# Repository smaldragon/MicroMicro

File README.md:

# MicroMicro

The MicroMicro (working name) is a project designed for a series I inteded(intend) to write, about how microcomputers work and how to go about developing one. It was designed to use a relatively small amount of integrated circuits (13), not use any programmable chips, microcontrollers or obselete parts, and to be a self-contained architecture that handles its own input and output (ie. not serial based).

With these requirements in mind, the overall specs are humble but capable:
* an 65c02 8bit cpu, running at 2Mhz
* 32KiB of ram, 8K of which are video ram
* 256x240 black and white display, via vga
* 1bit "beeper" audio
* Ultra-compact 30 Key keyboard using the "gherkin" layout
* Tape Interface for loading and storing data
* Cartridge port for rom programs and peripheral expansion
* 2 atari-style joystick ports

*Potential Features*
* custom case made from pcbs

The software side is still up in the air, but I'm aiming for the following features:
* A text editor
* An high-level programming language (undecided on which)
* A built-in assembler
* Saving and loading via the tape interface

This code would likely be custom and documented to follow the article structure of the hardware side of things.

# Memory Map

```
+---------------------+-------+-----------+
| Name                | Size  | Location  |
+---------------------+-------+-----------+
| Zero Page & Stack   | 512   | 0000-01FF |
| Video Data          | 7680  | 0200-1FFF |
| General Purpose RAM | 24576 | 2000-7FFF |
| IO Registers        | 8192  | 8000-9FFF |
| Expansion ROM       | 8192  | C000-DFFF |
| Bios ROM            | 8192  | E000-FFFF |
+---------------------+-------+-----------+ 
* the area from A000-BFFF is an invalid bus conflict region
```

## Video Data Format

Each byte corresonds to a line of 8 horizontal pixels on the screen. The screen addresses are organized as 32x30 character cells of 8x8 pixels each. 8 Consecutive bytes build one character.

This non-linear format was chosen to speed up the rendering of characters to the screen.

## Keyboard and Joystick

The state of the keyboard and joysticks can be read at the following addresses:

```
+---------------------+----------+-------------------------+
| Name                | Address  | Value (bits 0-5)        |
+---------------------+----------+-------------------------+
| Keyboard Col 1      |   9FFE   |  Q   A  Shf  z   S   W  |
| Keyboard Col 2      |   9FFD   |  E   D   X   C   F   R  |
| Keyboard Col 3      |   9FFB   |  T   G   V   B   H   Y  |
| Keyboard Col 4      |   9FF7   |  U   J   N   M   K   I  |
| Keyboard Col 5      |   9FEF   |  O   L  SPC ALT ENT  P  |
| Joystick 1          |   8FFF   |  ↑   ↓   ←   →   L   R  |
| Joystick 2          |   97FF   |  ↑   ↓   ←   →   L   R  |
+---------------------+----------+-------------------------+
```

## Beeper and Tape Interface

The Beeper is a 1bit register that is used for both audio generation and to load and save programs to tape. It can be accessed through the following registers:

```
+---------------------+-------------+-----------+
| Name                | Address     | Value     |
+---------------------+-------------+-----------+
| State               | 9FFF (read) | TB.. .... |
| Toggle Beeper       | FFFF (write)| 0000 0000 |
+---------------------+-------------+-----------+
T = Tape Input
B = Beeper State (top 2 bits of input register)
```

The tape interface is a 4-pin trs connector that be connected directly to a computer using an appropriate aux cable.

> Note: While these registers can be accessed from alternative locations, the addresses and values on this table ensure no bus conflicts occur.

## Expansion Interface

The MicroMicro has an expansion interface that allows extending the base capabilities of the system in various ways:

## Generic Banked Expansion Rom

An 8KiB region is set aside in the memory map for expansion roms (`$C000-$DFFF`), the emulator implements a simple banked rom cartridge where the current bank can be switched by reading from `$A0xx`, where `xx` is the bank number, the selected bank is also automatically set to zero on reset.

The bios will automatically jump to address `$C008` on boot if it detects an expansion rom that begins with the sring `CART-RUN`.

Currently expansion roms can be loaded by dragging and dropping a file into the emulator window.

## IC List

The design uses only 12 integrated circuits:

* `65c02` - 8bit CPU
* `62256` - 32KiB SRAM
* `39SF010 or 28C64 or 27C256` - 8KiB Program ROM
* `74hc10` - Tripple 3inNAND
* `74hc14` - Hex inverter
* `74hc32` - Quad 2inOR
* `74hc166` - 8bit parallel-to-serial shift register
* `74hc174` - 6bit d-type latch
* `74hc541` - 8bit buffer
* `74hc590`*2 - 8bit Counters
* `74hc4520`- Dual 4bit Counters

# Operating System

The 8k bios provides a simple command line operating system with the following commands:

| Command               | Description                                    |
| --------------------- | ---------------------------------------------- |
| `help`                | Lists all available commands                   |
| `clear`               | Clears the display                             |
| `file`                | The Size and Name of the currently loaded file |
| `new`                 | Create a new file                              |
| `name <name>`         | Rename the current file                        |
| `edit`                | Open the file editor                           |
| `save`                | Save file to tape                              |
| `load`                | Load file from tape                            |
| `run`    	            | Run Loaded File                                |
| `peek <addr> <bytes>` | Read contents of Memory                        |
| `poke <addr> <bytes>` | Write to Memory                                |
| `prun <addr>`         | Run a Machine Code Subroutine                  |

More info on the bios can be found [here](Docs/bios.md)

# Changelog

## A2

[Interactive BOM](https://raw.githack.com/smaldragon/MicroMicro/refs/heads/main/Kicad/a2/bom/ibom.html)

* Reset is now performed using a MCP-100 voltage supervisor, this primarly serves to replace the 74HC14 Schmitt Trigger Hex NOT with a 74HCT04, reducing delays, improving reliabiliy of the clock oscillator circuit, and freeing 1 NOT gate for the video circuit
* Video glitches (leftmost pixel column doubled on right, junk at the bottom of the screen) are now gone
* VGA video output is now better centered on the screen
* The small 6mm buzzer has been replaced with an header for a small speaker, improving volume and sound clarity
* Filtering capacitor added to data output
* Needless diodes removed
* Fixed footprint for headphone jack
* 2 additional M2 screw posts added to the center region of the board
* Schematic rearranged

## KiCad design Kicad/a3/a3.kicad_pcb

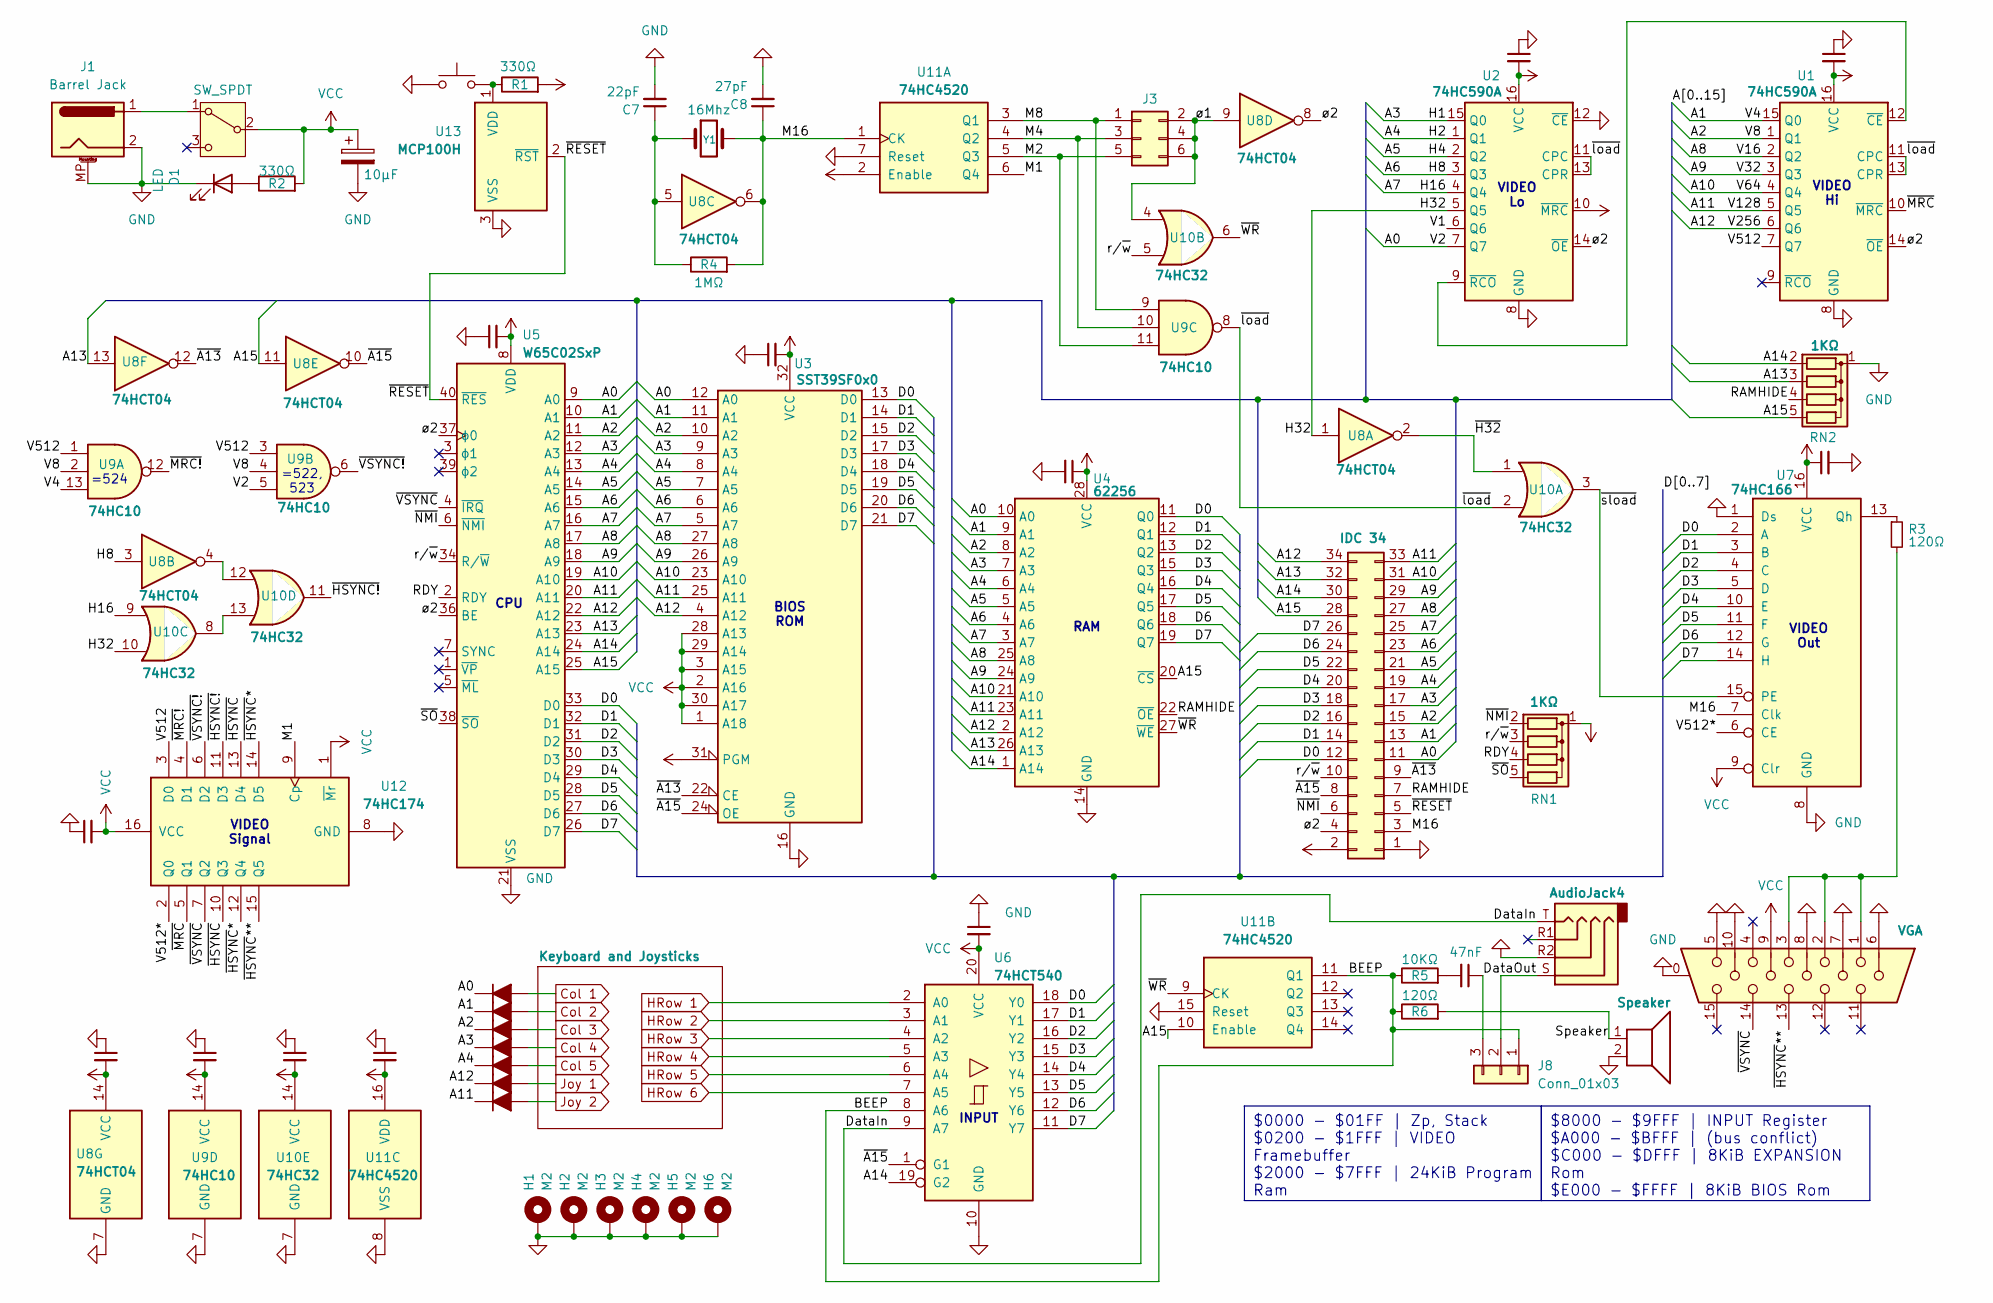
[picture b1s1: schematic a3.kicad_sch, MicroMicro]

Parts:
C1, C2, C3, C4, C5, C9, C11, C12, C14, C15, C16, C17: 100nF; C_Disc_D3.0mm_W1.6mm_P2.50mm
C6: 10µF; CP_Radial_D4.0mm_P1.50mm
C7: 22pF; C_Disc_D3.0mm_W1.6mm_P2.50mm
C8: 27pF; C_Disc_D3.0mm_W1.6mm_P2.50mm
C10: 47nF; C_Disc_D3.0mm_W1.6mm_P2.50mm
D1: LED; LED_Indicator_D3.0mm_W4.6mm_L6.5mm
D2, D3, D4, D5, D6, D12, D13: 1N4148; D_DO-35_SOD27_P7.62mm_Horizontal
H1, H2, H3, H4, H5, H6: M2; MountingHole_2.2mm_M2_ISO7380_Pad
J1: Barrel Jack; BarrelJack_GCT_DCJ200-10-A_Horizontal
J2: IDC 34; IDC-Header_2x17_P2.54mm_Horizontal
J3: Conn_02x03_Odd_Even; PinHeader_2x03_P2.54mm_Vertical
J4: VGA; DSUB-15-HD_Female_Horizontal_P2.29x1.98mm_EdgePinOffset3.03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
J5: AudioJack4; Jack_3.5mm_PJ320A_Horizontal
J8: Conn_01x03; PinHeader_1x03_P2.54mm_Vertical
LS1: Speaker; MagneticBuzzer_Kingstate_KCG0601
R1, R2: 330Ω; R_Axial_DIN0204_L3.6mm_D1.6mm_P2.54mm_Vertical
R3: 120Ω; R_Axial_DIN0204_L3.6mm_D1.6mm_P5.08mm_Horizontal
R4: 1MΩ; R_Axial_DIN0204_L3.6mm_D1.6mm_P7.62mm_Horizontal
R5: 10KΩ; R_Axial_DIN0204_L3.6mm_D1.6mm_P2.54mm_Vertical
R6: 120Ω; R_Axial_DIN0204_L3.6mm_D1.6mm_P2.54mm_Vertical
RN1, RN2: 1KΩ; R_Array_SIP5
SW1: SW_Push; SW_Tactile_SKHH_Angled
SW2: SW_SPDT; SW_Slide_SPDT_Angled_CK_OS102011MA1Q
U1, U2: 74HC590A; DIP-16_W7.62mm_LongPads
U3: SST39SF0x0; DIP-32_W15.24mm_LongPads
U4: 62256; DIP-28_W15.24mm_LongPads
U5: W65C02SxP; DIP-40_W15.24mm
U6: 74HCT540; DIP-20_W7.62mm_LongPads
U7: 74HC166; DIP-16_W7.62mm_LongPads
U8: 74HCT04; DIP-14_W7.62mm_LongPads
U9: 74HC10; DIP-14_W7.62mm_LongPads
U10: 74HC32; DIP-14_W7.62mm_LongPads
U11: 74HC4520; DIP-16_W7.62mm_LongPads
U12: 74HC174; DIP-16_W7.62mm_LongPads
U13: MCP100H; TO-92
Y1: 16Mhz; Crystal_HC49-4H_Vertical

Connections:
/A0: D2.1 (K), J2.11, U2.7 (Q7), U3.12 (A0), U4.10 (A0), U5.9 (A0), U9.5
/A1: D3.1 (K), J2.13, U1.15 (Q0), U3.11 (A1), U4.9 (A1), U5.10 (A1), U9.13
/A2: D4.1 (K), J2.15, U1.1 (Q1), U3.10 (A2), U4.8 (A2), U5.11 (A2), U9.2, U9.4
/A3: D5.1 (K), J2.17, U2.15 (Q0), U3.9 (A3), U4.7 (A3), U5.12 (A3)
/A4: D6.1 (K), J2.19, U2.1 (Q1), U3.8 (A4), U4.6 (A4), U5.13 (A4)
/A5: J2.21, U2.2 (Q2), U3.7 (A5), U4.5 (A5), U5.14 (A5)
/A6: J2.23, U2.3 (Q3), U3.6 (A6), U4.4 (A6), U5.15 (A6), U8.3
/A7: J2.25, U2.4 (Q4), U3.5 (A7), U4.3 (A7), U5.16 (A7), U10.9
/A8: J2.27, U1.2 (Q2), U3.27 (A8), U4.25 (A8), U5.17 (A8)
/A9: J2.29, U1.3 (Q3), U3.26 (A9), U4.24 (A9), U5.18 (A9)
/A10: J2.31, U1.4 (Q4), U3.23 (A10), U4.21 (A10), U5.19 (A10)
/A11: D13.1 (K), J2.33, U1.5 (Q5), U3.25 (A11), U4.23 (A11), U5.20 (A11)
/A12: D12.1 (K), J2.34, U1.6 (Q6), U3.4 (A12), U4.2 (A12), U5.22 (A12)
/A13: J2.32, RN2.3 (R2), U4.26 (A13), U5.23 (A13), U8.13
/A14: J2.30, RN2.2 (R1), U4.1 (A14), U5.24 (A14), U6.19 (G2)
/A15: J2.28, RN2.5 (R4), U4.20 (~CS), U5.25 (A15), U8.11, U11.10 (Enable)
/BEEP: J8.1, R5.1, R6.1, U6.8 (A6), U11.11 (Q1)
/D0: J2.12, U3.13 (D0), U4.11 (Q0), U5.33 (D0), U6.18 (Y0), U7.2 (A)
/D1: J2.14, U3.14 (D1), U4.12 (Q1), U5.32 (D1), U6.17 (Y1), U7.3 (B)
/D2: J2.16, U3.15 (D2), U4.13 (Q2), U5.31 (D2), U6.16 (Y2), U7.4 (C)
/D3: J2.18, U3.17 (D3), U4.15 (Q3), U5.30 (D3), U6.15 (Y3), U7.5 (D)
/D4: J2.20, U3.18 (D4), U4.16 (Q4), U5.29 (D4), U6.14 (Y4), U7.10 (E)
/D5: J2.22, U3.19 (D5), U4.17 (Q5), U5.28 (D5), U6.13 (Y5), U7.11 (F)
/D6: J2.24, U3.20 (D6), U4.18 (Q6), U5.27 (D6), U6.12 (Y6), U7.12 (G)
/D7: J2.26, U3.21 (D7), U4.19 (Q7), U5.26 (D7), U6.11 (Y7), U7.14 (H)
/DataIn: J5.T, U6.9 (A7)
/DataOut: J5.S, J8.2
/H32: U2.5 (Q5), U8.1, U10.10
/M1: U11.6 (Q4), U12.9 (Cp)
/M2: J3.5, U9.11, U11.5 (Q3)
/M4: J3.3, U9.10, U11.4 (Q2)
/M8: J3.1, U9.9, U11.3 (Q1)
/M16: C8.1, J2.3, R4.2, U7.7 (Clk), U8.6, U11.1 (CK), Y1.2
/RAMHIDE: J2.7, RN2.4 (R3), U4.22 (~OE)
/RDY: RN1.4 (R3), U5.2 (RDY)
/Speaker: LS1.1, R6.2
/V1: U2.6 (Q6)
/V512: U1.7 (Q7), U9.1, U9.3, U12.3 (D0)
/V512*: U7.6 (CE), U12.2 (Q0)
/r/~w: J2.10, RN1.3 (R2), U5.34 (R/~W), U10.5
/~A13: J2.9, U3.22 (CE), U8.12
/~A15: J2.8, U3.24 (OE), U6.1 (G1), U8.10
/~H32: U8.2, U10.1
/~HSYNC!: U10.11, U12.11 (D3)
/~HSYNC: U12.10 (Q3), U12.13 (D4)
/~HSYNC*: U12.12 (Q4), U12.14 (D5)
/~HSYNC**: J4.13, U12.15 (Q5)
/~MRC!: U9.12, U12.4 (D1)
/~MRC: U1.10 (~MRC), U12.5 (Q1)
/~NMI: J2.6, RN1.2 (R1), U5.6 (~NMI)
/~RESET: J2.5, U5.40 (~RES), U13.2 (~RST)
/~SO: RN1.5 (R4), U5.38 (~SO)
/~VSYNC!: U9.6, U12.6 (D2)
/~VSYNC: J4.14, U5.4 (~IRQ), U12.7 (Q2)
/~WR: U4.27 (~WE), U10.6, U11.9 (CK)
/~load: U1.11 (CPC), U1.13 (CPR), U2.11 (CPC), U2.13 (CPR), U9.8, U10.2
/~sload: U7.15 (PE), U10.3
/ø1: J3.2, J3.4, J3.6, U8.9, U10.4
/ø2: J2.4, U1.14 (~OE), U2.14 (~OE), U5.36 (BE), U5.37 (ϕ0), U8.8
Col 1: D2.2 (A); also elsewhere on the board
Col 2: D3.2 (A); also elsewhere on the board
Col 3: D4.2 (A); also elsewhere on the board
Col 4: D5.2 (A); also elsewhere on the board
Col 5: D6.2 (A); also elsewhere on the board
GND: C1.1, C2.1, C3.2, C4.2, C5.1, C6.2, C7.2, C8.2, C9.1, C11.1, C12.1, C14.1, C15.1, C16.1, C17.1, D1.1 (K), H1.1, H2.1, H3.1, H4.1, H5.1, H6.1, J1.2, J1.MP (MountPin), J2.1, J4.0, J4.5, J4.6, J4.7, J4.8, J4.10, J5.R2, LS1.2, RN2.1 (common), SW1.1, U1.8 (GND), U2.8 (GND), U2.12 (~CE), U3.16 (GND), U4.14 (GND), U5.21 (VSS), U6.10 (GND), U7.1 (Ds), U7.8 (GND), U8.7 (GND), U9.7 (GND), U10.7 (GND), U11.7 (Reset), U11.8 (VSS), U11.15 (Reset), U12.8 (GND), U13.3 (VSS); also elsewhere on the board
HRow 1: U6.2 (A0); also elsewhere on the board
HRow 2: U6.3 (A1); also elsewhere on the board
HRow 3: U6.4 (A2); also elsewhere on the board
HRow 4: U6.5 (A3); also elsewhere on the board
HRow 5: U6.6 (A4); also elsewhere on the board
HRow 6: U6.7 (A5); also elsewhere on the board
Joy 1: D12.2 (A); also elsewhere on the board
Joy 2: D13.2 (A); also elsewhere on the board
unnamed: C7.1, R4.1, U8.5, Y1.1
unnamed: C10.2, R5.2
unnamed: D1.2 (A), R2.1
unnamed: J4.1, J4.2, J4.3, R3.2
unnamed: C10.1, J8.3
unnamed: J1.1, SW2.1 (A)
unnamed: U1.12 (~CE), U2.9 (~RCO)
unnamed: R3.1, U7.13 (Qh)
unnamed: U8.4, U10.12
unnamed: U10.8, U10.13
unnamed: R1.1, SW1.2, U13.1 (VDD)
VCC: C1.2, C2.2, C3.1, C4.1, C5.2, C6.1, C9.2, C11.2, C12.2, C14.2, C15.2, C16.2, C17.2, J2.2, J4.9, R1.2, R2.2, RN1.1 (common), SW2.2 (B), U1.16 (VCC), U2.10 (~MRC), U2.16 (VCC), U3.1 (A18), U3.2 (A16), U3.3 (A15), U3.28 (A13), U3.29 (A14), U3.30 (A17), U3.31 (PGM), U3.32 (VCC), U4.28 (VCC), U5.8 (VDD), U6.20 (VCC), U7.9 (Clr), U7.16 (VCC), U8.14 (VCC), U9.14 (VCC), U10.14 (VCC), U11.2 (Enable), U11.16 (VDD), U12.1 (~Mr), U12.16 (VCC); also elsewhere on the board

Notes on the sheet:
VIDEO Lo
=524
BIOS ROM
VIDEO Signal
=522, 523
INPUT
RAM
VIDEO Out
VIDEO Hi
CPU
$8000 - $9FFF | INPUT Register $A000 - $BFFF | (bus conflict) $C000 - $DFFF | 8KiB EXPANSION Rom $E000 - $FFFF | 8KiB BIOS Rom
$0000 - $01FF | Zp, Stack $0200 - $1FFF | VIDEO Framebuffer $2000 - $7FFF | 24KiB Program Ram

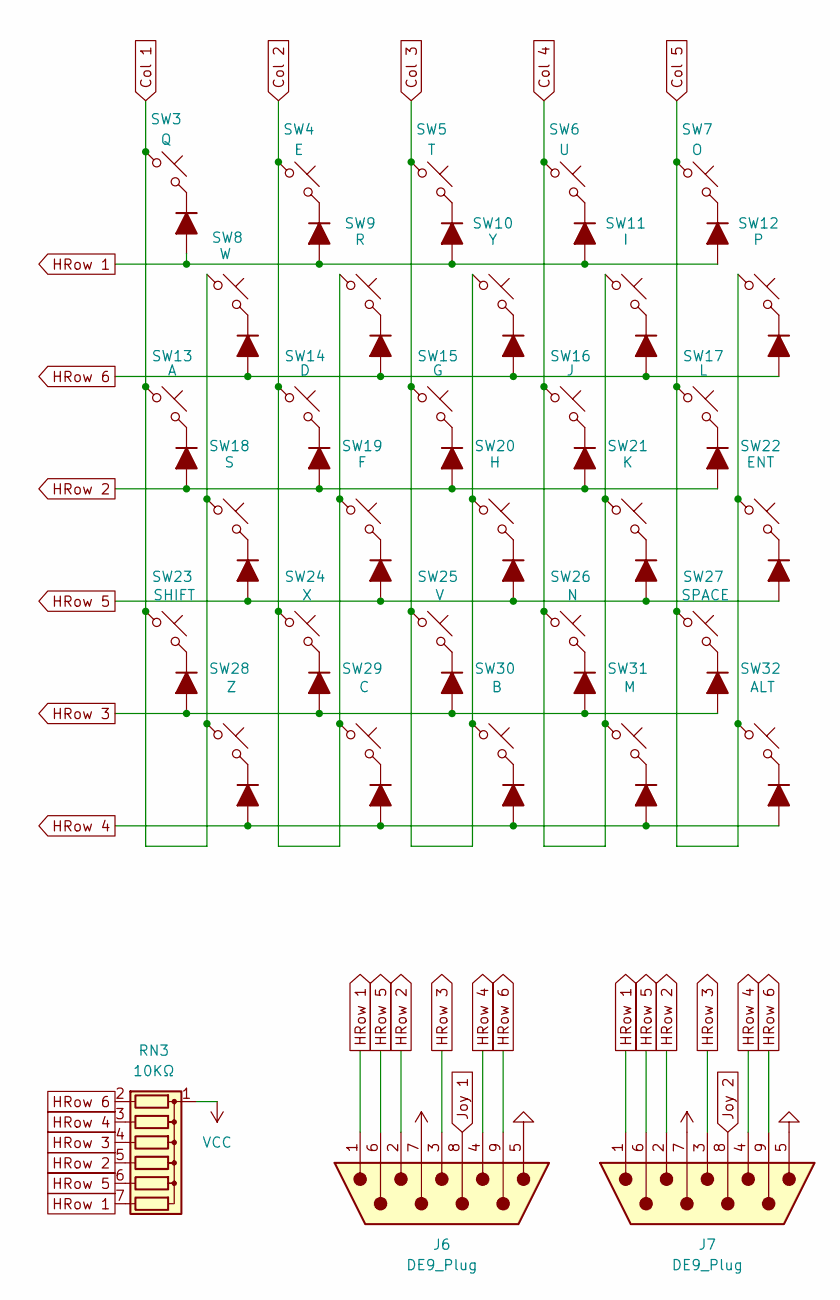
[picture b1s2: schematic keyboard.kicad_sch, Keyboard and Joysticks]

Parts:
D7, D8, D9, D10, D11, D14, D15, D16, D17, D18, D19, D20, D21, D22, D23, D24, D25, D26, D27, D28, D29, D30, D31, D32, D33, D34, D35, D36, D37, D38: 1N4148; D_DO-35_SOD27_P7.62mm_Horizontal
J6, J7: DE9_Plug; DSUB9-Atari
RN3: 10KΩ; R_Array_SIP7
SW3: Q; SW_Redragon_MX_LowProfile_PCB_1.00u_Other
SW4: E; SW_Redragon_MX_LowProfile_PCB_1.00u_Other
SW5: T; SW_Redragon_MX_LowProfile_PCB_1.00u_Other
SW6: U; SW_Redragon_MX_LowProfile_PCB_1.00u_Other
SW7: O; SW_Redragon_MX_LowProfile_PCB_1.00u_Other
SW8: W; SW_Redragon_MX_LowProfile_PCB_1.00u_Other
SW9: R; SW_Redragon_MX_LowProfile_PCB_1.00u_Other
SW10: Y; SW_Redragon_MX_LowProfile_PCB_1.00u_Other
SW11: I; SW_Redragon_MX_LowProfile_PCB_1.00u_Other
SW12: P; SW_Redragon_MX_LowProfile_PCB_1.00u_Other
SW13: A; SW_Redragon_MX_LowProfile_PCB_1.00u_Other
SW14: D; SW_Redragon_MX_LowProfile_PCB_1.00u_Other
SW15: G; SW_Redragon_MX_LowProfile_PCB_1.00u_Other
SW16: J; SW_Redragon_MX_LowProfile_PCB_1.00u_Other
SW17: L; SW_Redragon_MX_LowProfile_PCB_1.00u_Other
SW18: S; SW_Redragon_MX_LowProfile_PCB_1.00u_Other
SW19: F; SW_Redragon_MX_LowProfile_PCB_1.00u_Other
SW20: H; SW_Redragon_MX_LowProfile_PCB_1.00u_Other
SW21: K; SW_Redragon_MX_LowProfile_PCB_1.00u_Other
SW22: ENT; SW_Redragon_MX_LowProfile_PCB_1.00u_Other
SW23: SHIFT; SW_Redragon_MX_LowProfile_PCB_1.00u_Other
SW24: X; SW_Redragon_MX_LowProfile_PCB_1.00u_Other
SW25: V; SW_Redragon_MX_LowProfile_PCB_1.00u_Other
SW26: N; SW_Redragon_MX_LowProfile_PCB_1.00u_Other
SW27: SPACE; SW_Redragon_MX_LowProfile_PCB_1.00u_Other
SW28: Z; SW_Redragon_MX_LowProfile_PCB_1.00u_Other
SW29: C; SW_Redragon_MX_LowProfile_PCB_1.00u_Other
SW30: B; SW_Redragon_MX_LowProfile_PCB_1.00u_Other
SW31: M; SW_Redragon_MX_LowProfile_PCB_1.00u_Other
SW32: ALT; SW_Redragon_MX_LowProfile_PCB_1.00u_Other

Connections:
Col 1: SW3.1, SW8.1, SW13.1, SW18.1, SW23.1, SW28.1; also elsewhere on the board
Col 2: SW4.1, SW9.1, SW14.1, SW19.1, SW24.1, SW29.1; also elsewhere on the board
Col 3: SW5.1, SW10.1, SW15.1, SW20.1, SW25.1, SW30.1; also elsewhere on the board
Col 4: SW6.1, SW11.1, SW16.1, SW21.1, SW26.1, SW31.1; also elsewhere on the board
Col 5: SW7.1, SW12.1, SW17.1, SW22.1, SW27.1, SW32.1; also elsewhere on the board
GND: J6.5, J7.5; also elsewhere on the board
HRow 1: D7.2 (A), D8.2 (A), D9.2 (A), D10.2 (A), D11.2 (A), J6.1, J7.1, RN3.7 (R6); also elsewhere on the board
HRow 2: D19.2 (A), D20.2 (A), D21.2 (A), D22.2 (A), D23.2 (A), J6.2, J7.2, RN3.5 (R4); also elsewhere on the board
HRow 3: D29.2 (A), D30.2 (A), D31.2 (A), D32.2 (A), D33.2 (A), J6.3, J7.3, RN3.4 (R3); also elsewhere on the board
HRow 4: D34.2 (A), D35.2 (A), D36.2 (A), D37.2 (A), D38.2 (A), J6.4, J7.4, RN3.3 (R2); also elsewhere on the board
HRow 5: D24.2 (A), D25.2 (A), D26.2 (A), D27.2 (A), D28.2 (A), J6.6, J7.6, RN3.6 (R5); also elsewhere on the board
HRow 6: D14.2 (A), D15.2 (A), D16.2 (A), D17.2 (A), D18.2 (A), J6.9, J7.9, RN3.2 (R1); also elsewhere on the board
Joy 1: J6.8; also elsewhere on the board
Joy 2: J7.8; also elsewhere on the board
unnamed: D7.1 (K), SW3.2
unnamed: D8.1 (K), SW4.2
unnamed: D9.1 (K), SW5.2
unnamed: D10.1 (K), SW6.2
unnamed: D11.1 (K), SW7.2
unnamed: D14.1 (K), SW8.2
unnamed: D15.1 (K), SW9.2
unnamed: D16.1 (K), SW10.2
unnamed: D17.1 (K), SW11.2
unnamed: D18.1 (K), SW12.2
unnamed: D19.1 (K), SW13.2
unnamed: D20.1 (K), SW14.2
unnamed: D21.1 (K), SW15.2
unnamed: D22.1 (K), SW16.2
unnamed: D23.1 (K), SW17.2
unnamed: D24.1 (K), SW18.2
unnamed: D25.1 (K), SW19.2
unnamed: D26.1 (K), SW20.2
unnamed: D27.1 (K), SW21.2
unnamed: D28.1 (K), SW22.2
unnamed: D29.1 (K), SW23.2
unnamed: D30.1 (K), SW24.2
unnamed: D31.1 (K), SW25.2
unnamed: D32.1 (K), SW26.2
unnamed: D33.1 (K), SW27.2
unnamed: D34.1 (K), SW28.2
unnamed: D35.1 (K), SW29.2
unnamed: D36.1 (K), SW30.2
unnamed: D37.1 (K), SW31.2
unnamed: D38.1 (K), SW32.2
VCC: J6.7, J7.7, RN3.1 (common); also elsewhere on the board

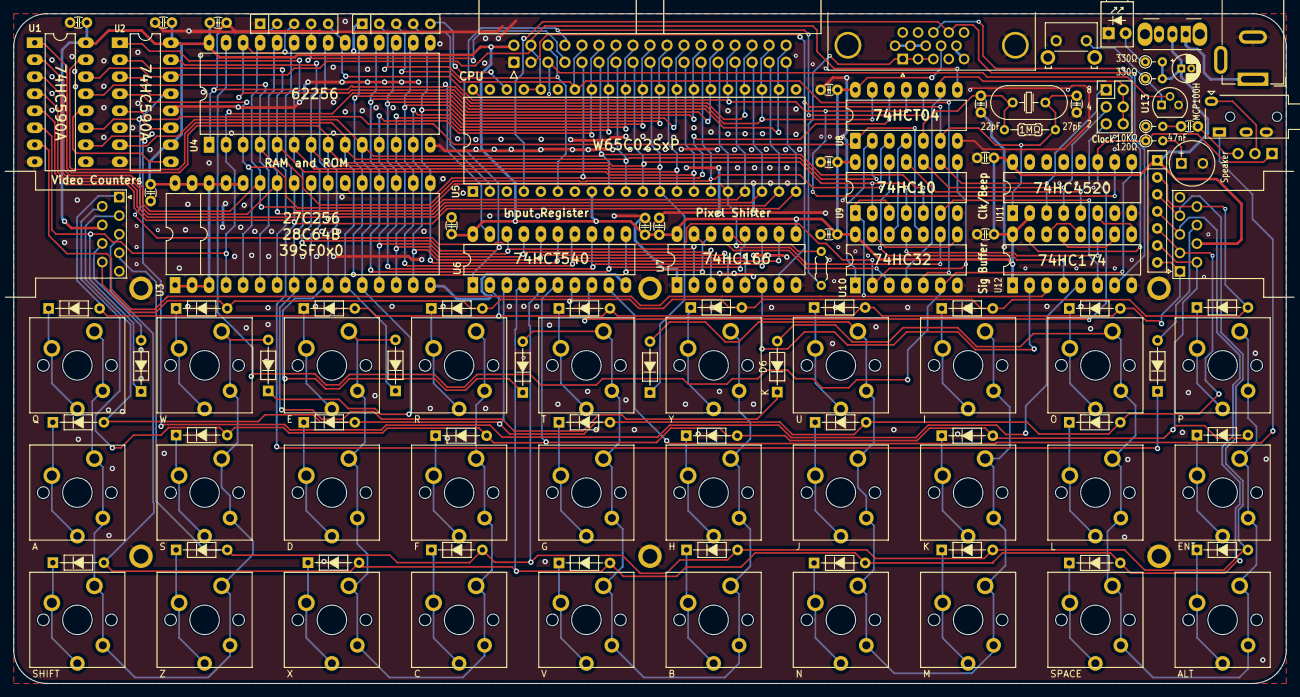
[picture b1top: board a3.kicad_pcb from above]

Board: 2 copper layers, 190.0 x 100.0 mm, 124 parts (1 on the bottom side), 114 nets.

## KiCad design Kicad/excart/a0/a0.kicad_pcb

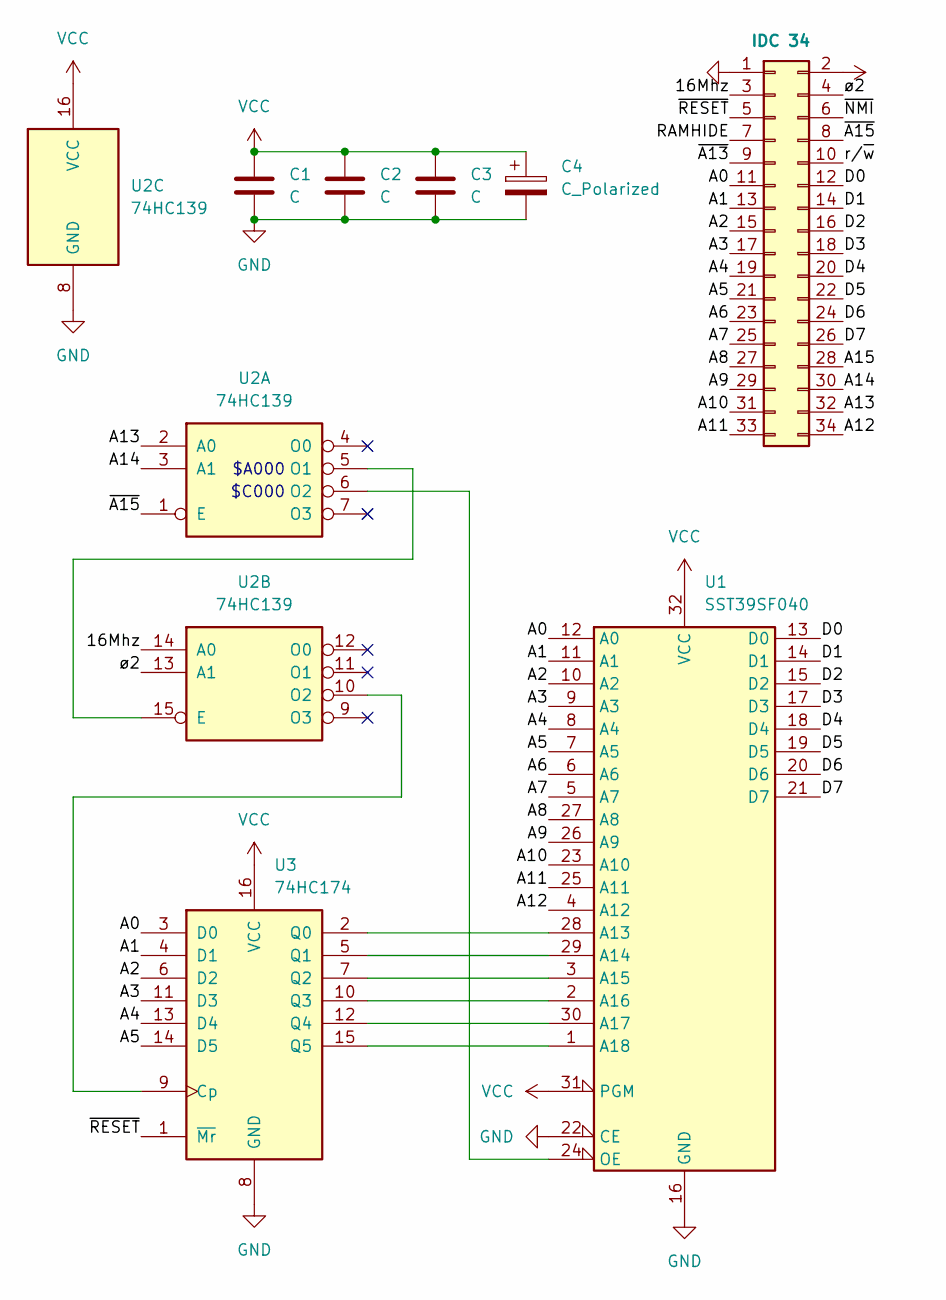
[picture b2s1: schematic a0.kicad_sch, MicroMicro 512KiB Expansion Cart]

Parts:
C1, C2, C3: C; C_Disc_D3.0mm_W1.6mm_P2.50mm
C4: C_Polarized; CP_Radial_D5.0mm_P2.50mm
J1: IDC 34; PinSocket_2x17_P2.54mm_Vertical
U1: SST39SF040; PLCC-DIP-32_THT-Socket
U2: 74HC139; DIP-16_W7.62mm
U3: 74HC174; DIP-16_W7.62mm

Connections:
/16Mhz: J1.3, U2.14 (A0)
/A0: J1.11, U1.12 (A0), U3.3 (D0)
/A1: J1.13, U1.11 (A1), U3.4 (D1)
/A2: J1.15, U1.10 (A2), U3.6 (D2)
/A3: J1.17, U1.9 (A3), U3.11 (D3)
/A4: J1.19, U1.8 (A4), U3.13 (D4)
/A5: J1.21, U1.7 (A5), U3.14 (D5)
/A6: J1.23, U1.6 (A6)
/A7: J1.25, U1.5 (A7)
/A8: J1.27, U1.27 (A8)
/A9: J1.29, U1.26 (A9)
/A10: J1.31, U1.23 (A10)
/A11: J1.33, U1.25 (A11)
/A12: J1.34, U1.4 (A12)
/A13: J1.32, U2.2 (A0)
/A14: J1.30, U2.3 (A1)
/A15: J1.28
/D0: J1.12, U1.13 (D0)
/D1: J1.14, U1.14 (D1)
/D2: J1.16, U1.15 (D2)
/D3: J1.18, U1.17 (D3)
/D4: J1.20, U1.18 (D4)
/D5: J1.22, U1.19 (D5)
/D6: J1.24, U1.20 (D6)
/D7: J1.26, U1.21 (D7)
/RAMHIDE: J1.7
/r/~w: J1.10
/~A13: J1.9
/~A15: J1.8, U2.1 (E)
/~NMI: J1.6
/~RESET: J1.5, U3.1 (~Mr)
/ø2: J1.4, U2.13 (A1)
GND: C1.2, C2.2, C3.2, C4.2, J1.1, U1.16 (GND), U1.22 (CE), U2.8 (GND), U3.8 (GND)
unnamed: U1.28 (A13), U3.2 (Q0)
unnamed: U1.29 (A14), U3.5 (Q1)
unnamed: U1.3 (A15), U3.7 (Q2)
unnamed: U1.2 (A16), U3.10 (Q3)
unnamed: U1.30 (A17), U3.12 (Q4)
unnamed: U1.1 (A18), U3.15 (Q5)
unnamed: U1.24 (OE), U2.6 (O2)
unnamed: U2.5 (O1), U2.15 (E)
unnamed: U2.10 (O2), U3.9 (Cp)
VCC: C1.1, C2.1, C3.1, C4.1, J1.2, U1.31 (PGM), U1.32 (VCC), U2.16 (VCC), U3.16 (VCC)

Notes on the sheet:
$A000
$C000

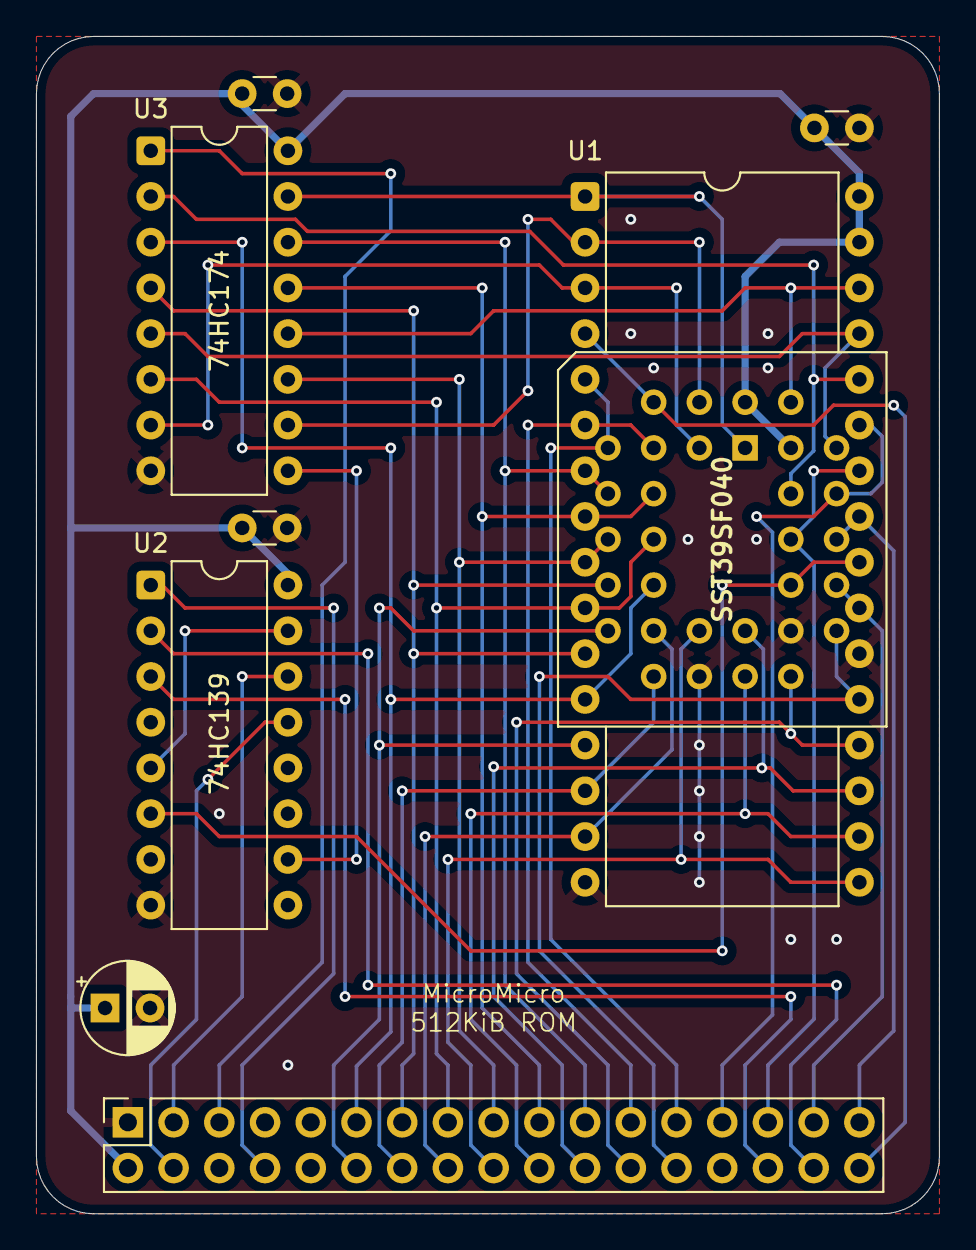
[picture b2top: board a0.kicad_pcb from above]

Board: 2 copper layers, 50.2 x 65.4 mm, 8 parts (0 on the bottom side), 38 nets.
